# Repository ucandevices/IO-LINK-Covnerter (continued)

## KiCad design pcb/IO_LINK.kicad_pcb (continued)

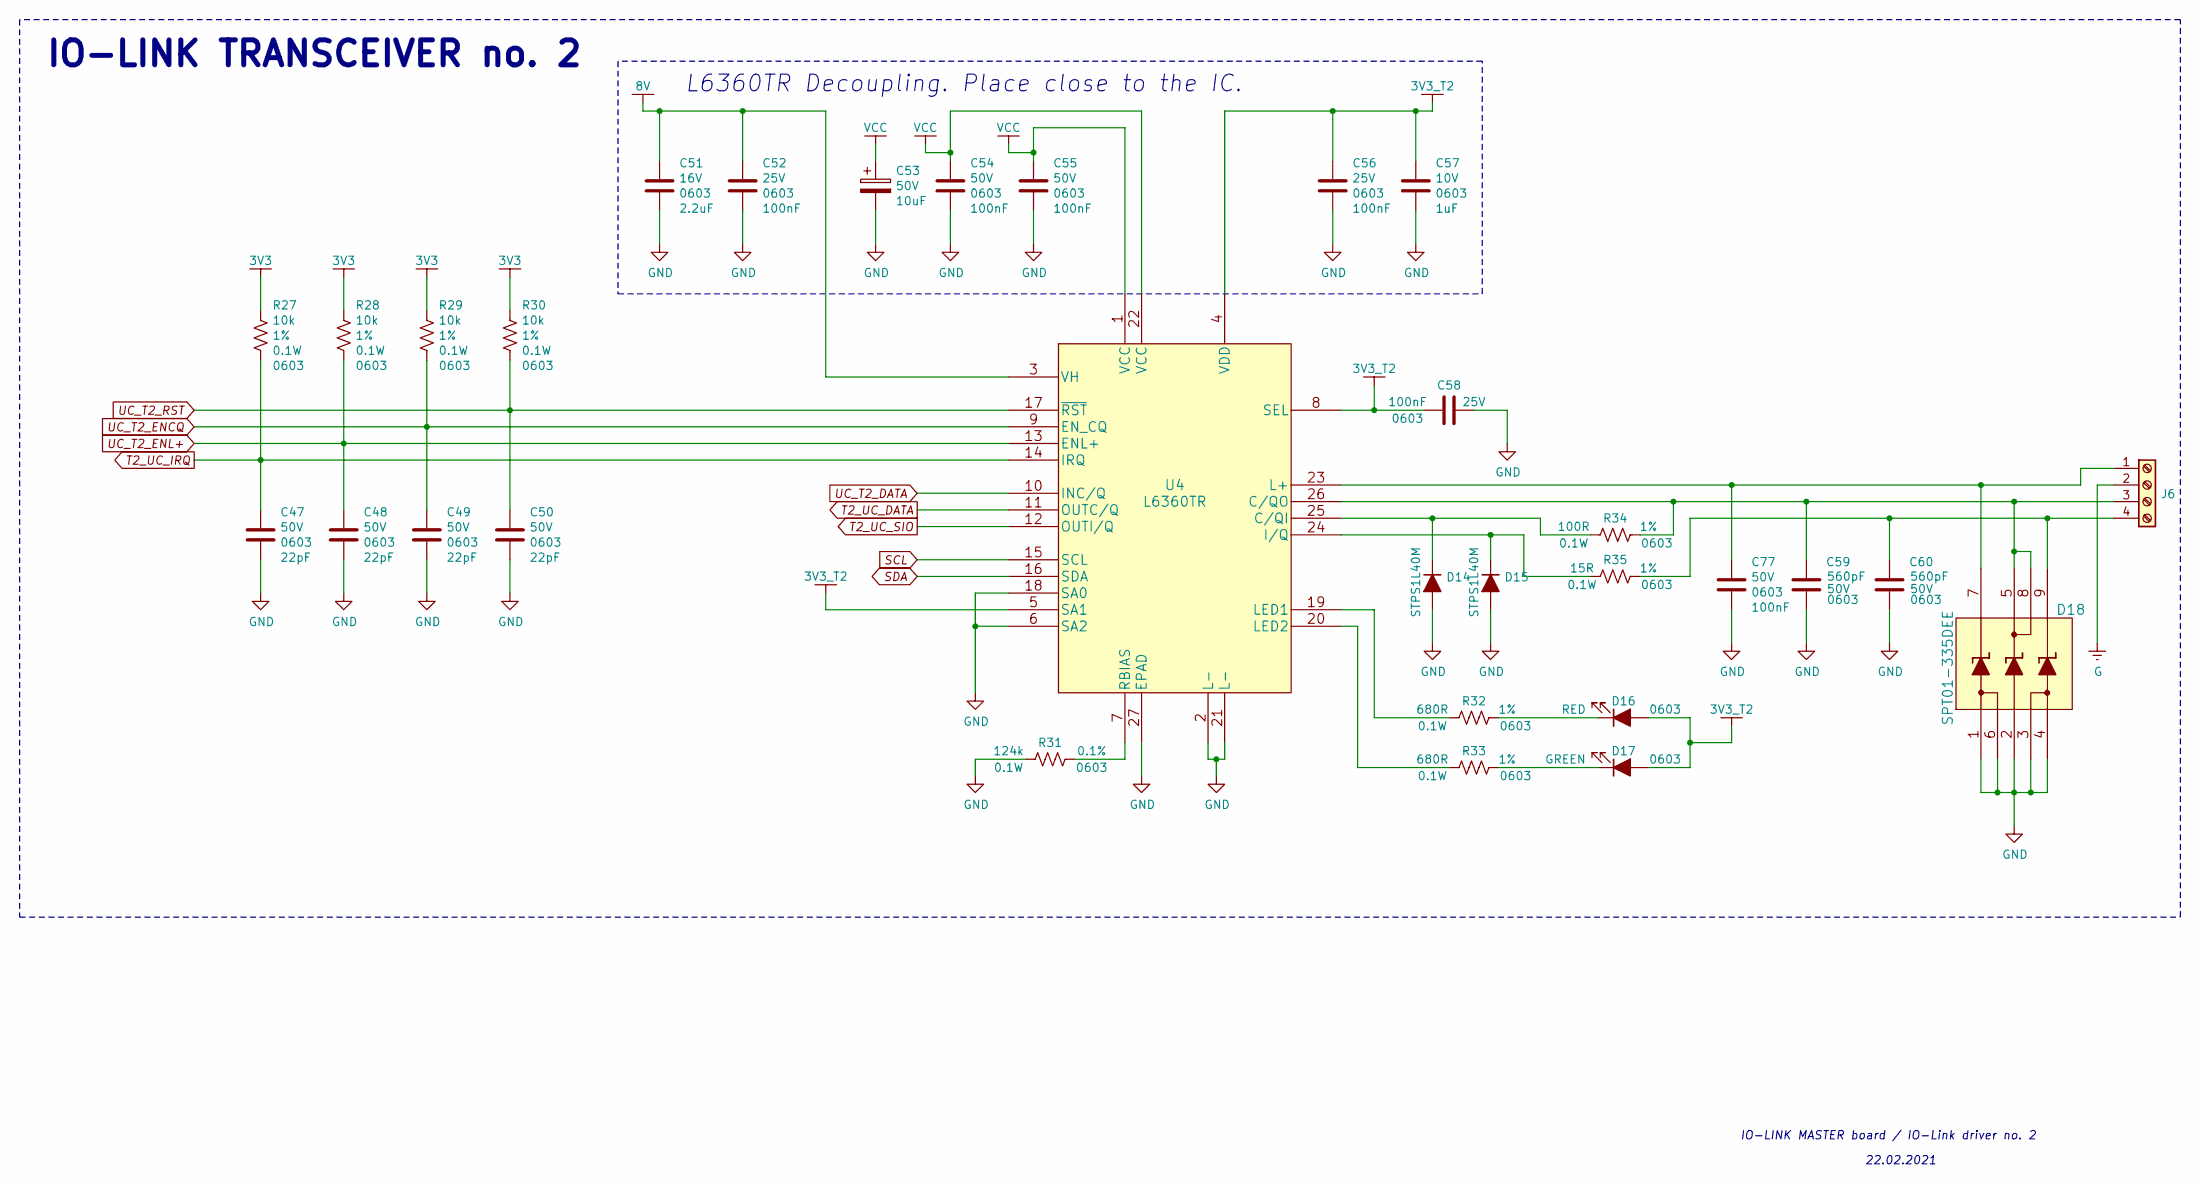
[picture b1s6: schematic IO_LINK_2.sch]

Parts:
C47, C48, C49, C50: 22pF_50V_0603; C_0603_1608Metric_Pad1.08x0.95mm_HandSolder; Voltage 50V; MPN CL10C220JB8NNNC; LCSC C1653
C51: 2.2uF_16V_0603; C_0603_1608Metric_Pad1.08x0.95mm_HandSolder; Voltage 16V; MPN CL10A225KO8NNNC; LCSC C23630
C52, C56, C58: 100nF_25V_0603; C_0603_1608Metric_Pad1.08x0.95mm_HandSolder; Voltage 25V; MPN 0603B104K250CT; LCSC C83054
C53: 10uF_50V_6.3mm_x_5.8mm_electrolytic; CP_Elec_6.3x5.8; Voltage 50V; MPN VZH100M1HTR-0606; LCSC C249820
C54, C55, C77: 100nF_50V_0603; C_0603_1608Metric_Pad1.08x0.95mm_HandSolder; Voltage 50V; MPN CC0603KRX7R9BB104; LCSC C14663
C57: 1uF_10V_0603; C_0603_1608Metric_Pad1.08x0.95mm_HandSolder; Voltage 10V; MPN CL10B105KP8NNNC; LCSC C95843
C59, C60: 560pF_50V_0603; C_0603_1608Metric_Pad1.08x0.95mm_HandSolder; Voltage 50V; MPN CL10B561KB8NNNC; LCSC C84721
D14, D15: STPS1L40M; DO-216; MPN STPS1L40M; LCSC N/A
D16: LED_RED; LED_0603; MPN 150060RS55040; LCSC N/A
D17: LED_GREEN; LED_0603; MPN 150060VS55040; LCSC N/A
D18: SPT01-335DEE; MPN SPT01-335DEE; LCSC N/A
J6: Screw_Terminal_01x04; TerminalBlock_Altech_AK300-4_P5.00mm; MPN 1715747; LCSC N/A
R27, R28, R29, R30: 10k_1%_0.1W_0603; R_0603_1608Metric_Pad0.98x0.95mm_HandSolder; Tolerance 1%; MPN 0603WAF1002T5E; LCSC C25804
R31: 124k_0.1%_0.1W_0603; R_0603_1608Metric_Pad0.98x0.95mm_HandSolder; Tolerance 0.1%; MPN RG1608P-1243-B-T5; LCSC N/A
R32, R33: 680R_1%_0.1W_0603; R_0603_1608Metric_Pad0.98x0.95mm_HandSolder; Tolerance 1%; MPN 0603WAF6800T5E; LCSC C23228
R34: 100R_1%_0.1W_0603; R_0603_1608Metric_Pad0.98x0.95mm_HandSolder; Tolerance 1%; MPN 0603WAF1000T5E; LCSC C22775
R35: 15R_1%_0.1W_0603; R_0603_1608Metric_Pad0.98x0.95mm_HandSolder; Tolerance 1%; MPN 0603WAF150JT5E; LCSC C22810
U4: L6360TR; MPN L6360TR; LCSC N/A

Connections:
3V3: R27.1, R28.1, R29.1, R30.1; also elsewhere on the board
3V3_T2: C56.1, C57.1, C58.2, D16.2 (A), D17.2 (A), U4.4 (VDD), U4.5 (SA1), U4.8 (SEL); also elsewhere on the board
8V: C51.1, C52.1, U4.3 (VH); also elsewhere on the board
G: J6.2; also elsewhere on the board
GND: C47.2, C48.2, C49.2, C50.2, C51.2, C52.2, C53.2, C54.2, C55.2, C56.2, C57.2, C58.1, C59.2, C60.2, C77.2, D14.2 (A), D15.2 (A), D18.1, D18.2, D18.3, D18.4, D18.6, R31.2, U4.2 (L-), U4.6 (SA2), U4.18 (SA0), U4.21 (L-), U4.27 (EPAD); also elsewhere on the board
unnamed: C59.1, D18.5, D18.8, J6.3, R34.1, U4.26 (C/QO)
unnamed: C60.1, D18.9, J6.4, R35.1
unnamed: C77.1, D18.7, J6.1, U4.23 (L+)
unnamed: D14.1 (K), R34.2, U4.25 (C/QI)
unnamed: D15.1 (K), R35.2, U4.24 (I/Q)
unnamed: D16.1 (K), R32.1
unnamed: D17.1 (K), R33.1
unnamed: R31.1, U4.7 (RBIAS)
unnamed: R32.2, U4.19 (LED1)
unnamed: R33.2, U4.20 (LED2)
SCL: U4.15 (SCL); also elsewhere on the board
SDA: U4.16 (SDA); also elsewhere on the board
T2_UC_DATA: U4.11 (OUTC/Q); also elsewhere on the board
T2_UC_IRQ: C47.1, R27.2, U4.14 (IRQ); also elsewhere on the board
T2_UC_SIO: U4.12 (OUTI/Q); also elsewhere on the board
UC_T2_DATA: U4.10 (INC/Q); also elsewhere on the board
UC_T2_ENCQ: C49.1, R29.2, U4.9 (EN_CQ); also elsewhere on the board
UC_T2_ENL+: C48.1, R28.2, U4.13 (ENL+); also elsewhere on the board
UC_T2_RST: C50.1, R30.2, U4.17 (~RST); also elsewhere on the board
VCC: C53.1, C54.1, C55.1, U4.1 (VCC), U4.22 (VCC); also elsewhere on the board

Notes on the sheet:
L6360TR Decoupling. Place close to the IC.
IO-LINK TRANSCEIVER no. 2
IO-LINK MASTER board / IO-Link driver no. 2
22.02.2021

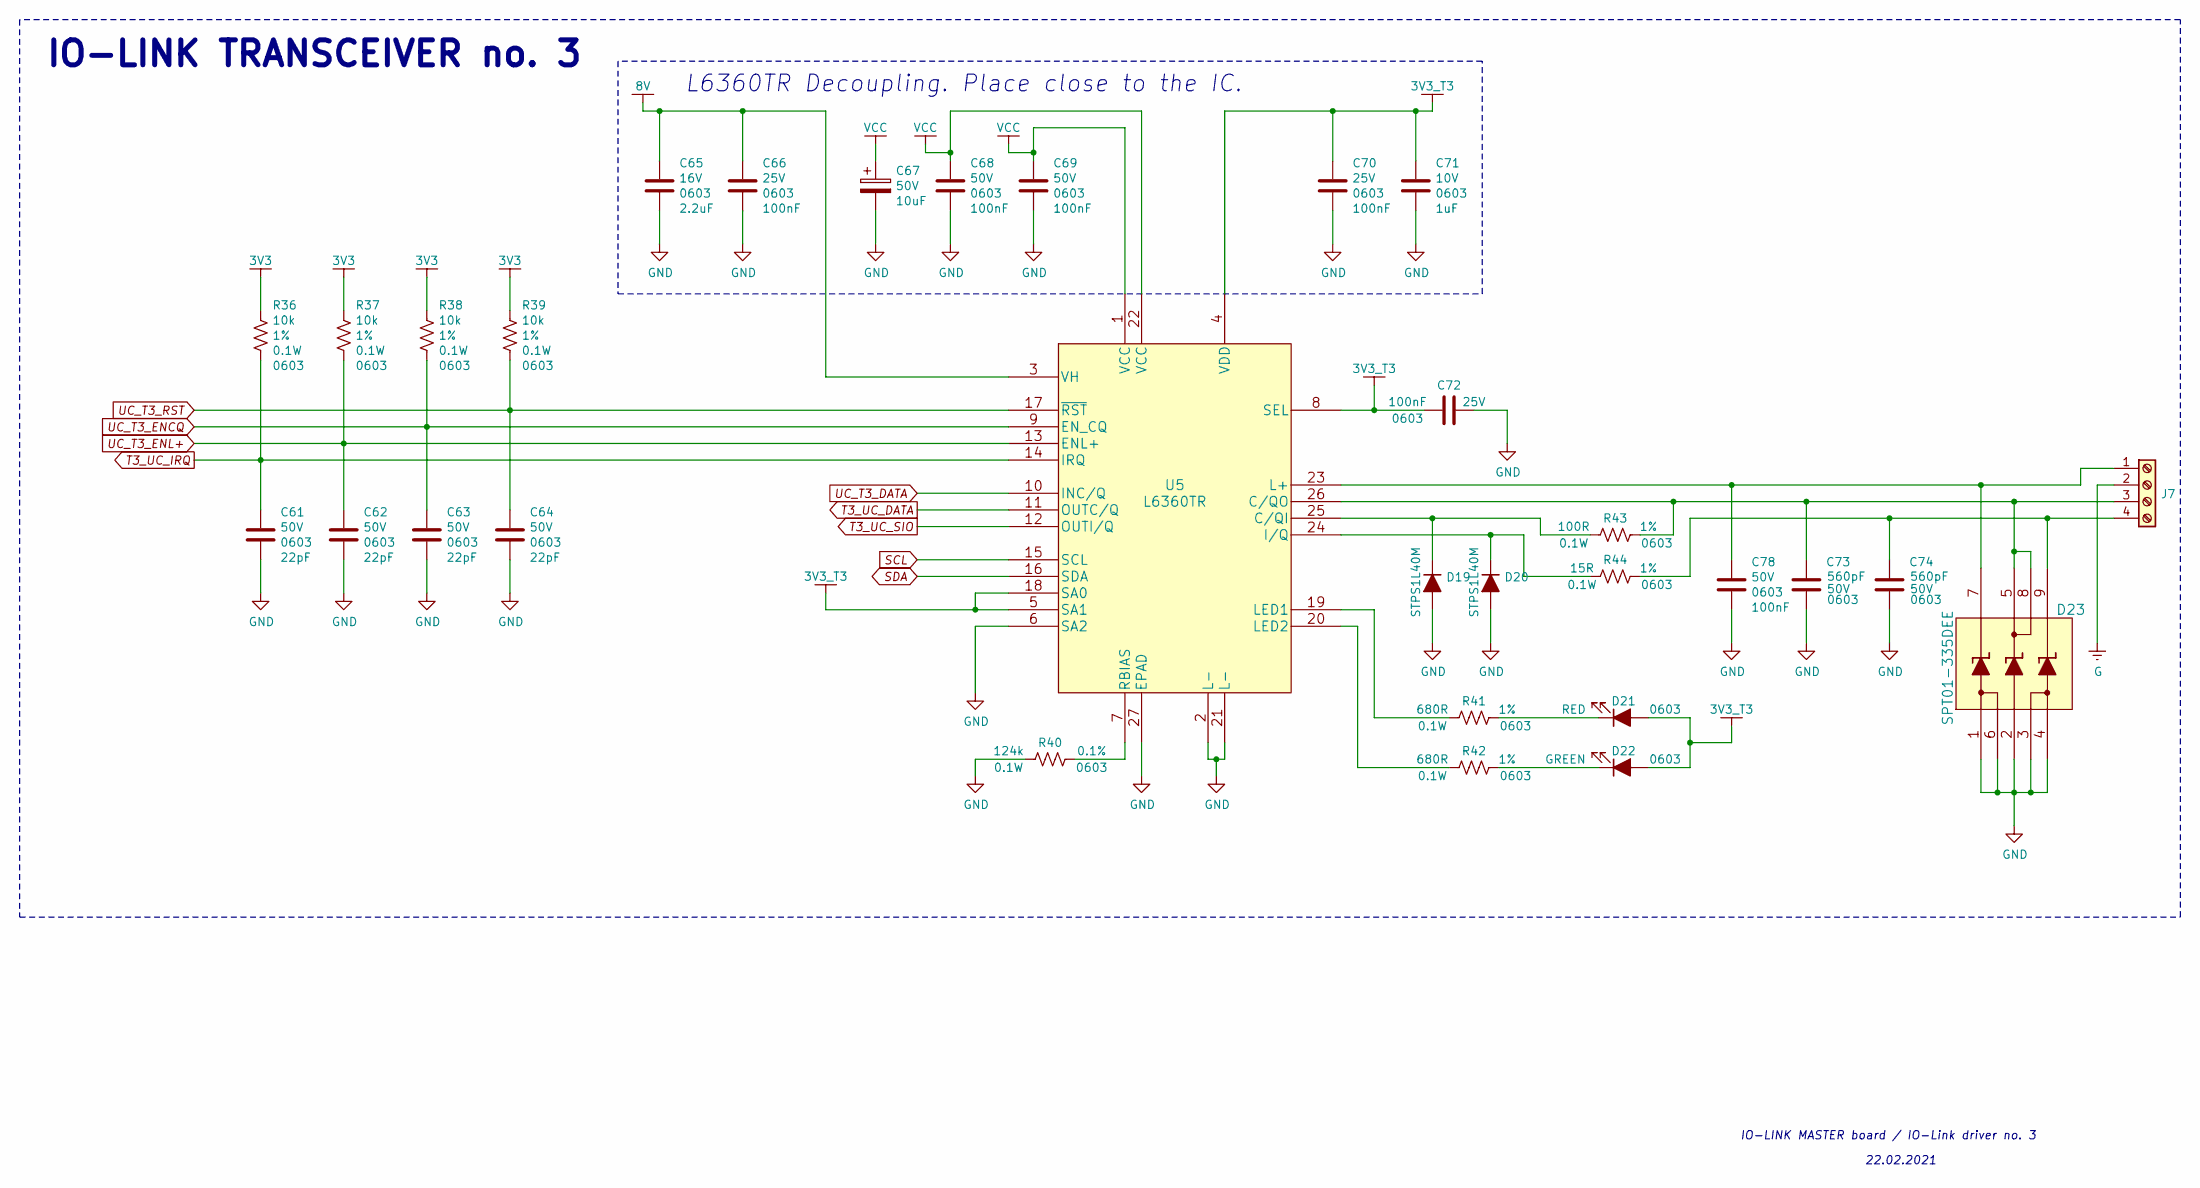
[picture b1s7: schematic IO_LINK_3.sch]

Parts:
C61, C62, C63, C64: 22pF_50V_0603; C_0603_1608Metric_Pad1.08x0.95mm_HandSolder; Voltage 50V; MPN CL10C220JB8NNNC; LCSC C1653
C65: 2.2uF_16V_0603; C_0603_1608Metric_Pad1.08x0.95mm_HandSolder; Voltage 16V; MPN CL10A225KO8NNNC; LCSC C23630
C66, C70, C72: 100nF_25V_0603; C_0603_1608Metric_Pad1.08x0.95mm_HandSolder; Voltage 25V; MPN 0603B104K250CT; LCSC C83054
C67: 10uF_50V_6.3mm_x_5.8mm_electrolytic; CP_Elec_6.3x5.8; Voltage 50V; MPN VZH100M1HTR-0606; LCSC C249820
C68, C69, C78: 100nF_50V_0603; C_0603_1608Metric_Pad1.08x0.95mm_HandSolder; Voltage 50V; MPN CC0603KRX7R9BB104; LCSC C14663
C71: 1uF_10V_0603; C_0603_1608Metric_Pad1.08x0.95mm_HandSolder; Voltage 10V; MPN CL10B105KP8NNNC; LCSC C95843
C73, C74: 560pF_50V_0603; C_0603_1608Metric_Pad1.08x0.95mm_HandSolder; Voltage 50V; MPN CL10B561KB8NNNC; LCSC C84721
D19, D20: STPS1L40M; DO-216; MPN STPS1L40M; LCSC N/A
D21: LED_RED; LED_0603; MPN 150060RS55040; LCSC N/A
D22: LED_GREEN; LED_0603; MPN 150060VS55040; LCSC N/A
D23: SPT01-335DEE; MPN SPT01-335DEE; LCSC N/A
J7: Screw_Terminal_01x04; TerminalBlock_Altech_AK300-4_P5.00mm; MPN 1715747; LCSC N/A
R36, R37, R38, R39: 10k_1%_0.1W_0603; R_0603_1608Metric_Pad0.98x0.95mm_HandSolder; Tolerance 1%; MPN 0603WAF1002T5E; LCSC C25804
R40: 124k_0.1%_0.1W_0603; R_0603_1608Metric_Pad0.98x0.95mm_HandSolder; Tolerance 0.1%; MPN RG1608P-1243-B-T5; LCSC N/A
R41, R42: 680R_1%_0.1W_0603; R_0603_1608Metric_Pad0.98x0.95mm_HandSolder; Tolerance 1%; MPN 0603WAF6800T5E; LCSC C23228
R43: 100R_1%_0.1W_0603; R_0603_1608Metric_Pad0.98x0.95mm_HandSolder; Tolerance 1%; MPN 0603WAF1000T5E; LCSC C22775
R44: 15R_1%_0.1W_0603; R_0603_1608Metric_Pad0.98x0.95mm_HandSolder; Tolerance 1%; MPN 0603WAF150JT5E; LCSC C22810
U5: L6360TR; MPN L6360TR; LCSC N/A

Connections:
3V3: R36.1, R37.1, R38.1, R39.1; also elsewhere on the board
3V3_T3: C70.1, C71.1, C72.2, D21.2 (A), D22.2 (A), U5.4 (VDD), U5.5 (SA1), U5.8 (SEL), U5.18 (SA0); also elsewhere on the board
8V: C65.1, C66.1, U5.3 (VH); also elsewhere on the board
G: J7.2; also elsewhere on the board
GND: C61.2, C62.2, C63.2, C64.2, C65.2, C66.2, C67.2, C68.2, C69.2, C70.2, C71.2, C72.1, C73.2, C74.2, C78.2, D19.2 (A), D20.2 (A), D23.1, D23.2, D23.3, D23.4, D23.6, R40.2, U5.2 (L-), U5.6 (SA2), U5.21 (L-), U5.27 (EPAD); also elsewhere on the board
unnamed: C73.1, D23.5, D23.8, J7.3, R43.1, U5.26 (C/QO)
unnamed: C74.1, D23.9, J7.4, R44.1
unnamed: C78.1, D23.7, J7.1, U5.23 (L+)
unnamed: D19.1 (K), R43.2, U5.25 (C/QI)
unnamed: D20.1 (K), R44.2, U5.24 (I/Q)
unnamed: D21.1 (K), R41.1
unnamed: D22.1 (K), R42.1
unnamed: R40.1, U5.7 (RBIAS)
unnamed: R41.2, U5.19 (LED1)
unnamed: R42.2, U5.20 (LED2)
SCL: U5.15 (SCL); also elsewhere on the board
SDA: U5.16 (SDA); also elsewhere on the board
T3_UC_DATA: U5.11 (OUTC/Q); also elsewhere on the board
T3_UC_IRQ: C61.1, R36.2, U5.14 (IRQ); also elsewhere on the board
T3_UC_SIO: U5.12 (OUTI/Q); also elsewhere on the board
UC_T3_DATA: U5.10 (INC/Q); also elsewhere on the board
UC_T3_ENCQ: C63.1, R38.2, U5.9 (EN_CQ); also elsewhere on the board
UC_T3_ENL+: C62.1, R37.2, U5.13 (ENL+); also elsewhere on the board
UC_T3_RST: C64.1, R39.2, U5.17 (~RST); also elsewhere on the board
VCC: C67.1, C68.1, C69.1, U5.1 (VCC), U5.22 (VCC); also elsewhere on the board

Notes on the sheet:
L6360TR Decoupling. Place close to the IC.
IO-LINK TRANSCEIVER no. 3
IO-LINK MASTER board / IO-Link driver no. 3
22.02.2021

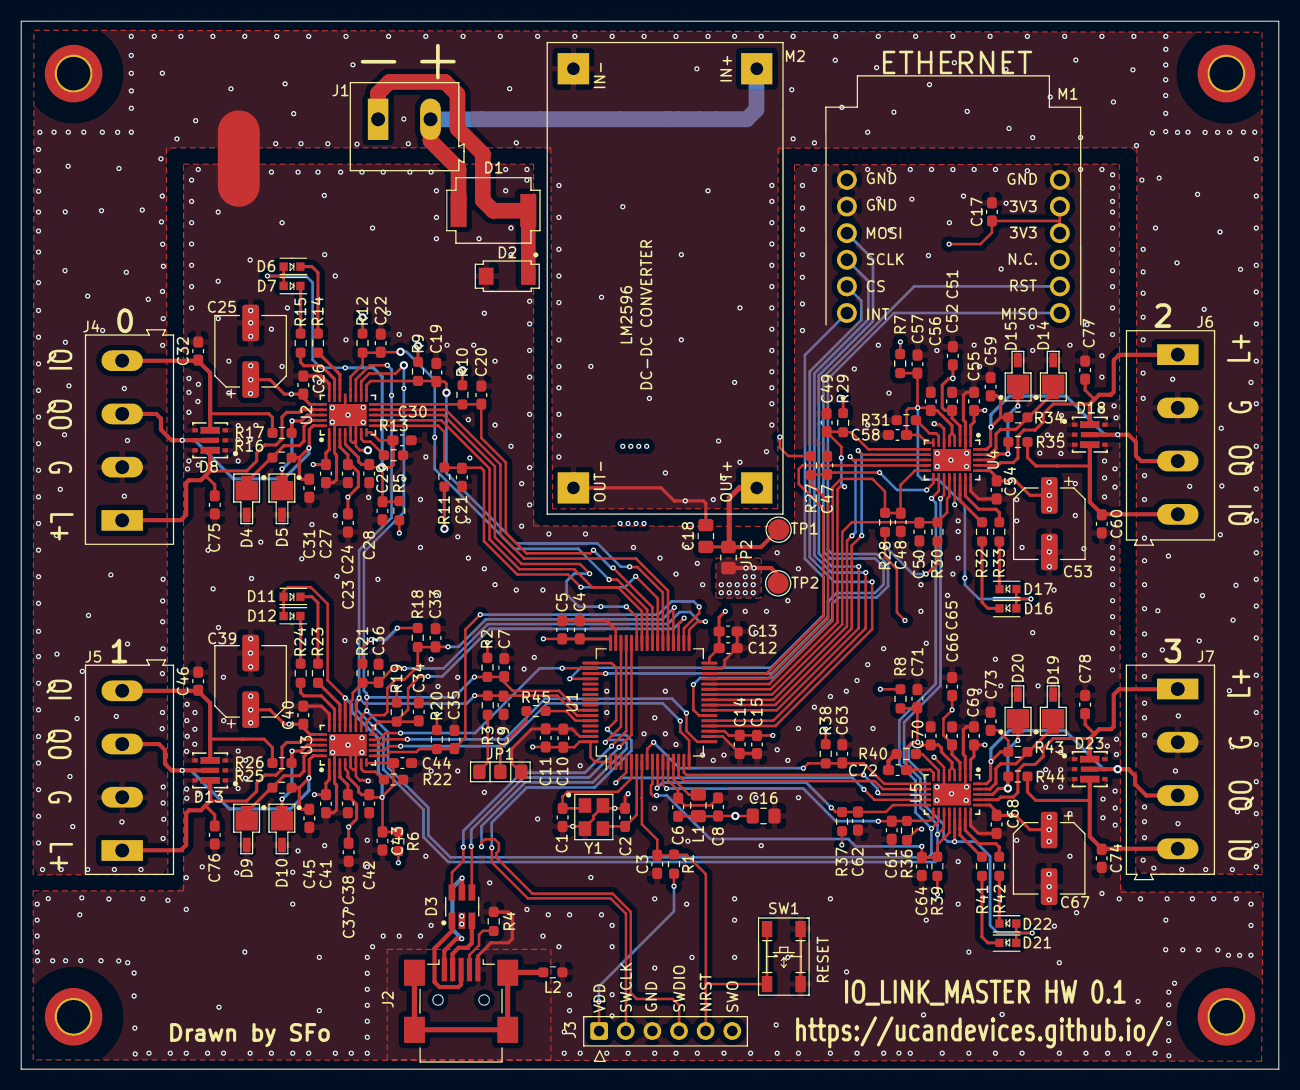
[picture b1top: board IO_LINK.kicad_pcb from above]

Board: 4 copper layers, 120.0 x 100.0 mm, 172 parts (0 on the bottom side), 102 nets.

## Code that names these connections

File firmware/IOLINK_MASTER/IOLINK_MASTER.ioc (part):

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PB13.GPIOParameters=GPIO_Speed,GPIO_Label
PA6.Mode=Full_Duplex_Master
PC7.GPIOParameters=GPIO_PuPd,GPIO_Label
Mcu.UserName=STM32F072RBTx
PC10.Signal=GPIO_Output
PB14.GPIO_Label=UC_T1_ENL
PC0.GPIOParameters=GPIO_Speed,GPIO_Label
PC0.GPIO_Label=UC_T3_ENCQ
PC6.GPIO_Label=T0_UC_SIO
PA11.Mode=Device
PB0.GPIO_Label=UC_T2_RST
PC5.Mode=Asynchronous
PB13.GPIO_Label=UC_T1_ENCQ
PB11.Signal=GPIO_Input
PB13.Signal=GPIO_Output
PB15.Signal=GPIO_Input
PC15-OSC32_OUT.GPIO_Label=T3_UC_SIO
RCC.SYSCLKSource=RCC_SYSCLKSOURCE_HSI48
PA15.GPIO_Label=T1_UC_SIO
PA12.Signal=USB_DP
PC1.GPIOParameters=PinState,GPIO_Label,GPIO_ModeDefaultOutputPP
PB0.PinState=GPIO_PIN_SET
PB6.Signal=I2C1_SCL
PC7.Signal=GPIO_Input
PB12.PinState=GPIO_PIN_SET
PB6.Mode=I2C
PC3.Signal=GPIO_Input
PA8.GPIOParameters=PinState,GPIO_Label,GPIO_ModeDefaultOutputPP
PC1.PinState=GPIO_PIN_SET
RCC.HSE_VALUE=16000000
PB2.Signal=GPIO_Output
PB12.GPIO_ModeDefaultOutputPP=GPIO_MODE_OUTPUT_OD
PB12.GPIO_Label=UC_T1_RST
PB0.GPIOParameters=PinState,GPIO_Label,GPIO_ModeDefaultOutputPP
PB1.GPIO_Speed=GPIO_SPEED_FREQ_HIGH
PA14.Mode=Serial_Wire
PB1.GPIO_Label=UC_T2_ENCQ
PC11.GPIO_Label=INT_ETH
PA0.Mode=Asynchronous
PB3.GPIOParameters=GPIO_Label
PB7.Signal=I2C1_SDA
PA8.Signal=GPIO_Output
PA8.GPIO_ModeDefaultOutputPP=GPIO_MODE_OUTPUT_OD
PA0.Signal=USART4_TX
PC8.GPIOParameters=GPIO_Speed,GPIO_Label
Mcu.Package=LQFP64
PB9.Signal=GPIO_Output
PB1.Signal=GPIO_Output
PA6.Signal=SPI1_MISO
PA10.Signal=USART1_RX
PA15.Signal=GPIO_Input
PC8.GPIO_Speed=GPIO_SPEED_FREQ_HIGH
PB14.GPIOParameters=GPIO_Label
PB0.GPIO_ModeDefaultOutputPP=GPIO_MODE_OUTPUT_OD
PC5.Signal=USART3_RX
PB10.GPIOParameters=GPIO_Label
PC15-OSC32_OUT.GPIOParameters=GPIO_Label
PF1-OSC_OUT.Mode=HSE-External-Oscillator
PA4.GPIO_Label=CS_ETH
PC2.GPIO_Label=UC_T3_ENL
PF1-OSC_OUT.Signal=RCC_OSC_OUT
PC4.Mode=Asynchronous
PA8.PinState=GPIO_PIN_SET
PA3.Signal=USART2_RX
PA5.Mode=Full_Duplex_Master
PB3.GPIO_Label=L_ON
PA7.Mode=Full_Duplex_Master
PB9.GPIO_Label=USB_ENABLE
PA10.Mode=Asynchronous
PA15.GPIOParameters=GPIO_Label
PC10.GPIO_Label=RST_ETH
PC9.GPIO_Label=UC_T0_ENL
PC11.Signal=GPIO_Input
PC8.Signal=GPIO_Output
PC2.Signal=GPIO_Output
PC4.Signal=USART3_TX
PC6.Signal=GPIO_Input
PB11.GPIO_Label=T2_UC_SIO
PC0.Signal=GPIO_Output
PC11.GPIOParameters=GPIO_Label
PB9.GPIOParameters=GPIO_Label
PC3.GPIOParameters=GPIO_Label
PC8.GPIO_Label=UC_T0_ENCQ
PA3.Mode=Asynchronous
PA13.Signal=SYS_SWDIO
PA9.Mode=Asynchronous
PC0.GPIO_Speed=GPIO_SPEED_FREQ_HIGH
PA8.GPIO_Label=UC_T0_RST
PB10.GPIO_Label=T2_UC_IRQ
PB2.GPIOParameters=GPIO_Label
PA9.Signal=USART1_TX
PB13.GPIO_Speed=GPIO_SPEED_FREQ_HIGH
PB11.GPIOParameters=GPIO_Label
PC7.GPIO_PuPd=GPIO_NOPULL
PC15-OSC32_OUT.Signal=GPIO_Input
PA1.Signal=USART4_RX
PF0-OSC_IN.Mode=HSE-External-Oscillator
PB10.Signal=GPIO_Input
PB14.Signal=GPIO_Output
PA5.Signal=SPI1_SCK
board=custom
PA1.Mode=Asynchronous
PB15.GPIO_Label=T1_UC_IRQ
PC2.GPIOParameters=GPIO_Label
PC1.GPIO_Label=UC_T3_RST
PA4.GPIOParameters=GPIO_Label
PC10.GPIOParameters=GPIO_Label
PB15.GPIOParameters=GPIO_Label
PA13.Mode=Serial_Wire
PC9.GPIOParameters=GPIO_Label
Mcu.Name=STM32F072R(8-B)Tx
PA2.Signal=USART2_TX
PC7.GPIO_Label=T0_UC_IRQ
PB3.Signal=GPIO_Output
PA4.Signal=GPIO_Output
RCC.SYSCLKFreq_VALUE=48000000
PA12.Mode=Device
PA11.Signal=USB_DM
PB7.Mode=I2C
PA14.Signal=SYS_SWCLK
PB2.GPIO_Label=UC_T2_ENL
PC6.GPIOParameters=GPIO_Label
PC1.GPIO_ModeDefaultOutputPP=GPIO_MODE_OUTPUT_OD
PA2.Mode=Asynchronous
PC3.GPIO_Label=T3_UC_IRQ
PC9.Signal=GPIO_Output
PF0-OSC_IN.Signal=RCC_OSC_IN
PB0.Signal=GPIO_Output
PC1.Signal=GPIO_Output
PB12.GPIOParameters=PinState,GPIO_Label,GPIO_ModeDefaultOutputPP
PB12.Signal=GPIO_Output
PB1.GPIOParameters=GPIO_Speed,GPIO_Label
PA7.Signal=SPI1_MOSI

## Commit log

2021-02-13 Add folder structure
2021-02-22 Update MCU configuration
2021-03-03 Add files via upload
    First version of PCB board for IO-Link project. Minor (mostly esthetic) changes are still required, but the overall shape of the board and the schematic are has been finished.
    PCB is also free of relevant DRC bugs.
2021-03-06 Update Libs for PCb
2021-06-09 Testing lib for IO-Link
2021-06-15 Update example fo 08H222
2021-06-21 Add test software
2021-06-21 PCB Release
2021-06-30 Addition of Headers to SendData API
2021-06-30 added RX to sendDataIO_PORT_NUMBER
